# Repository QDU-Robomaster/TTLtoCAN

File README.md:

# 项目名称
TTLtoCANforTOF

## 项目简介
面向 ToF 设备的 TTL UART 转 CAN 通信模块，设计目标是通过 24V 输入为 ToF 提供 5V 电源，并由 STM32 完成串口数据与 CAN 报文之间的转换。

## PCB预览

以下预览基于 2026-10-05 21:07 保存的 PCB 文件重新生成。部分器件未配置三维模型，实际装配以封装和 BOM 为准。

正面：

背面：

## 主要参数
PCB 尺寸  36.00 × 20.05 mm，圆角矩形 
层数 / 板厚  2 层 / 1.6 mm 
输入电源  设计标称 24V，经 J4 输入 
ToF 电源  设计目标 5V，经 J3 第 4 脚输出 
板上逻辑电源  3.3V 
主控  STM32G0B1CBTx，LQFP-48 
通信接口  UART（J3）、CAN（J2） 
调试接口  SWD（J6） 
## 接口定义
J4：电源输入 AMASS XT30U-F，2Pin  
    1：GND；
    2：VCC_IN（标称 24V 输入） 
J2：CAN  JST GH，2Pin，1.25 mm  
    1：CAN− / CAN_L；
    2：CAN+ / CAN_H 
J3：ToF  JST GH，4Pin，1.25 mm  
    1：USART1_TX（模块输出，接设备 RX）；
    2：USART1_RX（模块输入，接设备 TX）；
    3：GND；
    4：5V 电源输出 
J6：SWD  Molex CLIK-Mate 502386-0470，4Pin，1.25 mm  
    1：SWDIO；
    2：SWCLK；
    3：GND；
    4：3.3V 参考电源 
## 项目扩展叙述

电源部分通过 TPS54202 将输入电源降压至设计目标 5V，再由 ME6211 产生板上 3.3V。STM32 连接 ToF 的 UART，并通过 CAN 收发器接入总线。通信转换需要配套固件，当前仓库未提供固件及协议定义。

详细的接口接线、工程打开方式、生产资料与调试安排见 [工程说明文档](Documents/工程说明.md)。

## 主要器件
U1  TPS54202DDC  开关降压，设计用于产生 5V 
U2  ME6211C33M5  3.3V 线性稳压 
U3  STM32G0B1CBTx  通信处理主控 
U6  TCAN3413DR（当前 Value）  CAN 收发器
Q2  Si2309CDS-T1-GE3  输入侧 P 沟道 MOS 管 
D3  BZT52-C12  输入保护电路中的稳压管 
L1  15µH  降压电感 
Y1  X32258MSB  MCU 外部晶振
## 制造资料指路
制造和装配输出位于 [Production_documents/](Production_documents/)，各子目录用途见 [工程说明文档](Documents/工程说明.md)。
使用 KiCad 10.0.x 打开根目录的 [TTLtoCANforTOF.kicad_pro](TTLtoCANforTOF.kicad_pro)，再进入原理图或 PCB 编辑器。
 [TTLtoCANforTOF.kicad_sch](TTLtoCANforTOF.kicad_sch)  当前原理图 
 [TTLtoCANforTOF.kicad_pcb](TTLtoCANforTOF.kicad_pcb)  当前 PCB 
 [sym-lib-table](sym-lib-table)  项目符号库路径配置  [BOM/](BOM/)  设计物料清单 
 [Documents/](Documents/)  项目说明、预览图和检查报告 
 [3Dmodel/TTLtoCANforTOF.step](3Dmodel/TTLtoCANforTOF.step)  整板 STEP 模型 
 [Production_documents/](Production_documents/)  生产输出资料 
 [History/](History/)  历史工程快照，不作为当前生产依据

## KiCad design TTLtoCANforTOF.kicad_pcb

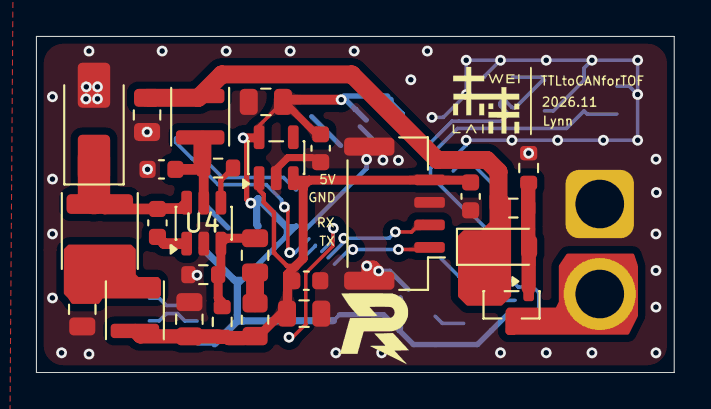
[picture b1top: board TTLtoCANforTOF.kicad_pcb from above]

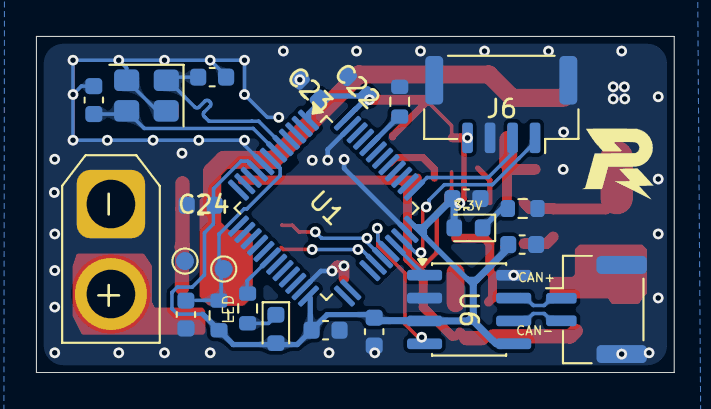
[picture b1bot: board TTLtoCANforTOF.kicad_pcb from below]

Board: 2 copper layers, 35.4 x 18.7 mm, 50 parts (24 on the bottom side), 28 nets.

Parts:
C1, C2, C10, C12, C13, C18, C19, C20, C21, C22, C23, C24: 0.1uF; C_0603_1608Metric
C3: 4.7uF; C_0805_2012Metric
C4: C_Small; C_0805_2012Metric
C5, C6, C9: 10uF; C_0805_2012Metric
C11: 22uF; C_0805_2012Metric
C15: 4.7uF; C_0603_1608Metric
C16, C17: 22pF; C_0603_1608Metric
D1, D2: LED; LED_0603_1608Metric
D3: BZT52-C12; D_SOD-123
D4: SS16; D_SMA
J2: CAN; JST_GH_BM02B-GHS-TBT_1x02-1MP_P1.25mm_Vertical
J3: TOF; JST_GH_BM04B-GHS-TBT_1x04-1MP_P1.25mm_Vertical
J4: XT30; AMASS_XT30U-F_1x02_P5.0mm_Vertical
J6: SWD; Molex_CLIK-Mate_502386-0470_1x04-1MP_P1.25mm_Horizontal
L1, L3: 10uH; L_Changjiang_FNR3010S
L2: 15uH; L_Changjiang_FNR4020S
Q2: Si2309CDS-T1-GE3; SOT-23
R1: 1MΩ; R_0603_1608Metric
R2: R_Small; R_0805_2012Metric
R4: 62kΩ; R_0603_1608Metric
R5: 12kΩ; R_0603_1608Metric
R6, R8: 10kΩ; R_0603_1608Metric
R7, R9: 100kΩ; R_0603_1608Metric
R10, R11: 1kΩ; R_0603_1608Metric
TP1: RST; TestPoint_Pad_D1.0mm
TP2: GND; TestPoint_Pad_D1.0mm
U1: STM32F103C8Tx; LQFP-48_7x7mm_P0.5mm
U2: ME6211C33M5; SOT-23-5
U4: TD1466tr; SOT-23-6
U6: TCAN3413DR; SOIC-8_3.9x4.9mm_P1.27mm
Y1: X32258MSB; Crystal_SMD_3225-4Pin_3.2x2.5mm

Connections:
5V: C6.2, C9.1, C10.1, C20.2, J3.4, L3.2, R2.2, R4.1, U2.1 (V_{IN}), U2.3 (CE)
+3.3V: C11.1, C12.1, C13.1, C15.1, C19.1, C21.1, C22.1, C23.1, C24.1, D1.2 (A), D2.2 (A), J6.4, R6.1, U1.1 (VBAT), U1.9 (VDDA), U1.24 (VDD), U1.36 (VDD), U1.48 (VDD), U2.5 (V_{OUT}), U6.3 (VCC), U6.5 (VIO)
+24V: C3.2, D3.1 (K), L1.1, Q2.2 (S), R9.1
/CAN+: J2.1, U6.7 (CANH)
/CAN-: J2.2, U6.6 (CANL)
/CAN_RX: U1.32 (PA11), U6.4 (RXD)
/CAN_TX: U1.33 (PA12), U6.1 (TXD)
/LED: R11.2, U1.18 (PB0)
/NRST: C18.1, R6.2, TP1.1 (1_1), U1.7 (NRST)
/OSC+: C16.2, U1.5 (PD0), Y1.1
/OSC-: C17.2, U1.6 (PD1), Y1.3
/SWCLK: J6.2, U1.37 (PA14)
/SWDIO: J6.1, U1.34 (PA13)
/USART1_RX: J3.2, U1.31 (PA10)
/USART1_TX: J3.1, U1.30 (PA9)
GND: C2.1, C3.1, C5.1, C6.1, C9.2, C10.2, C11.2, C12.2, C13.2, C15.2, C16.1, C17.1, C18.2, C19.2, C20.1, C21.2, C22.2, C23.2, C24.2, D4.2 (A), J2.MP (MountPin), J3.3, J3.MP (MountPin), J4.1, J6.3, J6.MP (MountPin), R5.2, R7.1, R8.1, R10.2, TP2.1 (1_1), U1.8 (VSSA), U1.23 (VSS), U1.35 (VSS), U1.47 (VSS), U2.2 (V_{SS}), U4.2 (GND), U6.2 (GND), U6.8 (STB), Y1.2, Y1.4
unnamed: C4.2, R2.1
unnamed: C5.2, L2.1, L3.1
unnamed: D1.1 (K), R10.1
unnamed: D2.1 (K), R11.1
unnamed: D3.2 (A), Q2.1 (G), R8.2, R9.2
unnamed: C1.2, D4.1 (K), L2.2, U4.6 (SW)
unnamed: R7.2, U1.44 (BOOT0)
unnamed: C1.1, U4.1 (BS)
unnamed: R1.2, U4.4 (EN)
unnamed: C4.1, R4.2, R5.1, U4.3 (FB)
unnamed: C2.2, L1.2, R1.1, U4.5 (VIN)
VCC_IN: J4.2, Q2.3 (D)

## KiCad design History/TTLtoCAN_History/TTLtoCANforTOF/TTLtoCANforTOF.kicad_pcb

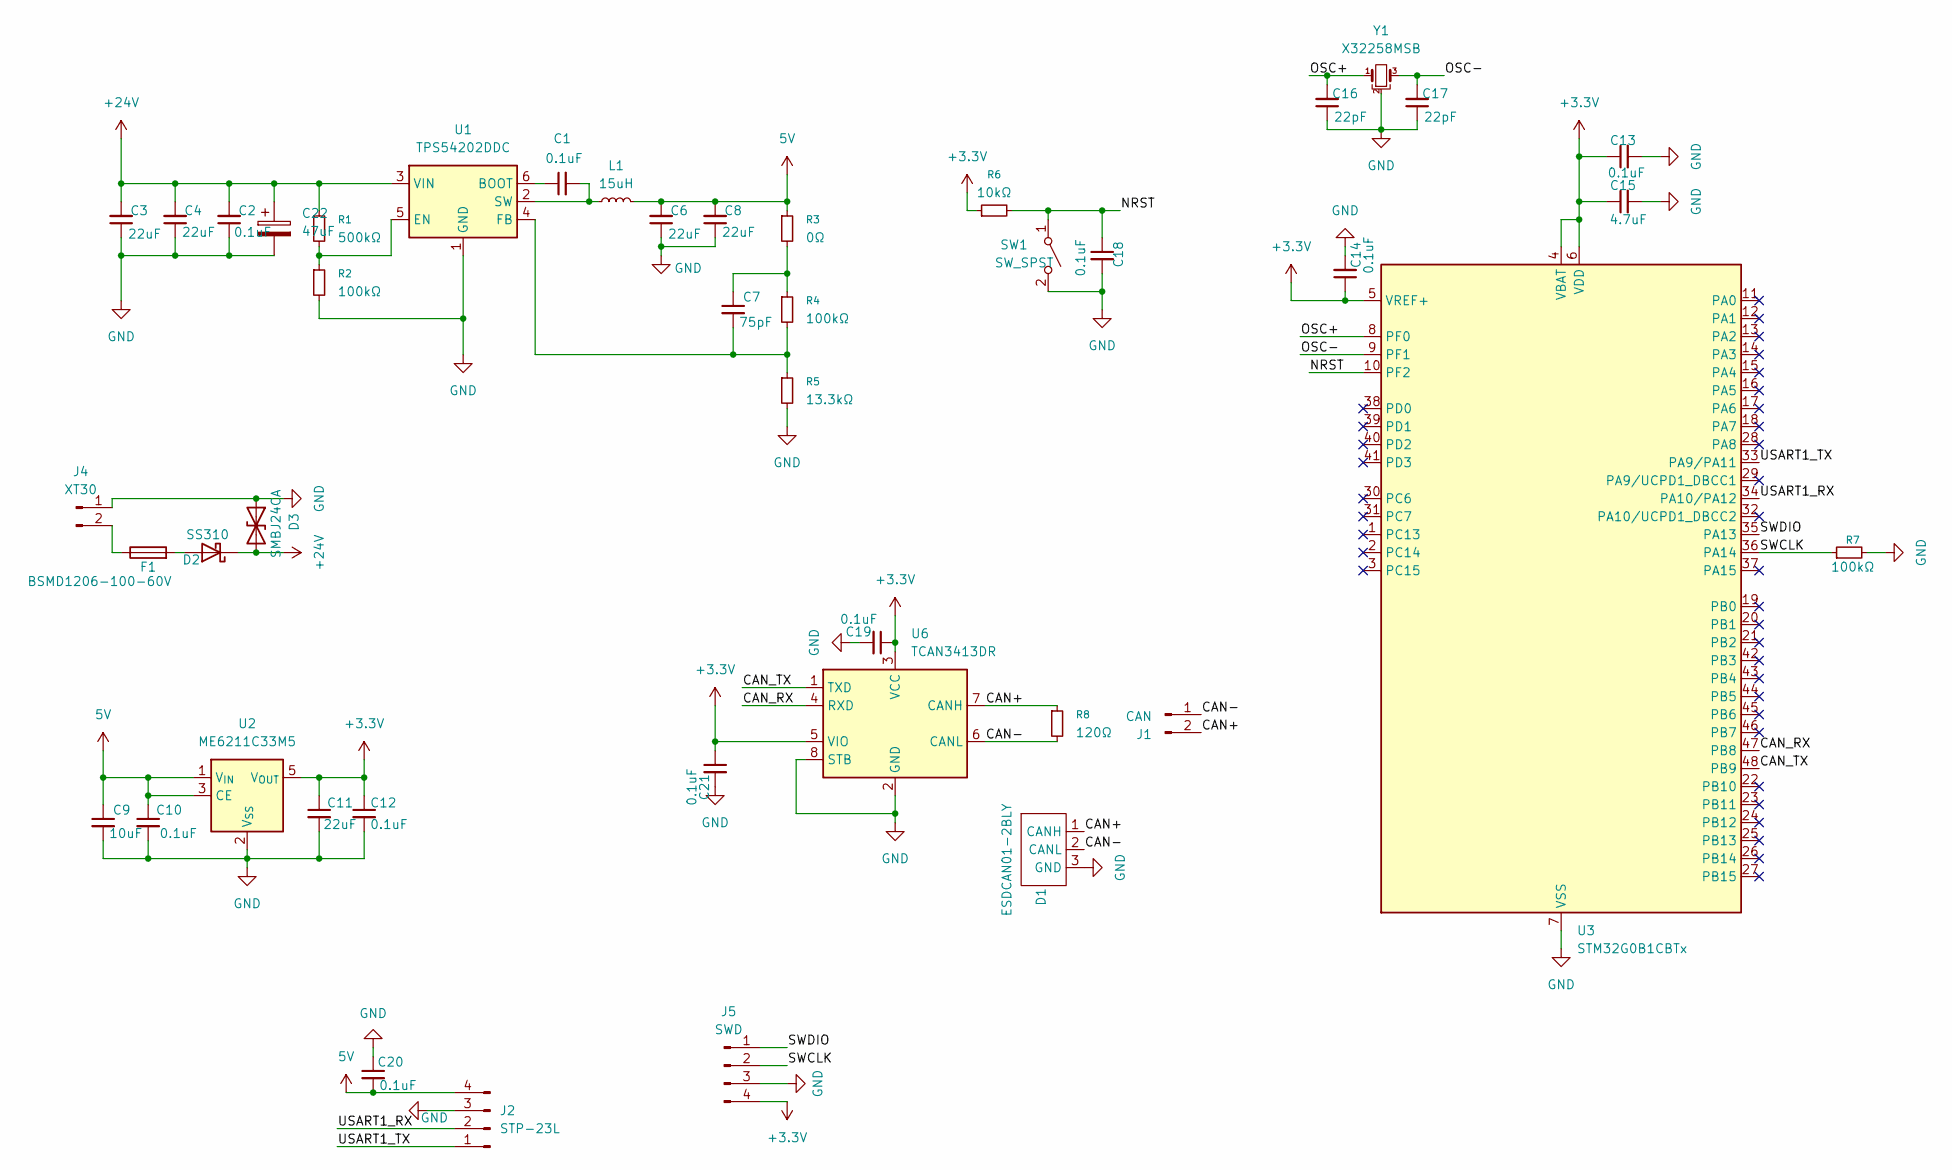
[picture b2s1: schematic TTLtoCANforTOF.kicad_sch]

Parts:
C1, C2, C10, C12, C13, C14, C18, C19, C20, C21: 0.1uF; C_0603_1608Metric
C3, C4: 22uF; C_1210_3225Metric
C6, C8, C11: 22uF; C_0805_2012Metric
C7: 75pF; C_0603_1608Metric
C9: 10uF; C_0805_2012Metric
C15: 4.7uF; C_0603_1608Metric
C16, C17: 22pF; C_0603_1608Metric
C22: 47uF; C_Elec_6.3x7.7
D1: ESDCAN01-2BLY; SOT-23-3
D2: SS310; D_SMA
D3: SMBJ24CA; D_SMB
F1: BSMD1206-100-60V; Fuse_1206_3216Metric
J1: CAN; JST_GH_SM02B-GHS-TB_1x02-1MP_P1.25mm_Horizontal
J2: STP-23L; JST_GH_SM04B-GHS-TB_1x04-1MP_P1.25mm_Horizontal
J4: XT30; AMASS_XT30U-F_1x02_P5.0mm_Vertical
J5: SWD; Molex_CLIK-Mate_502386-0470_1x04-1MP_P1.25mm_Horizontal
L1: 15uH; L_7.3x7.3_H3.5
R1: 500kΩ; R_0603_1608Metric
R2, R4, R7: 100kΩ; R_0603_1608Metric
R3: 0Ω; R_0805_2012Metric
R5: 13.3kΩ; R_0603_1608Metric
R6: 10kΩ; R_0603_1608Metric
R8: 120Ω; R_1206_3216Metric
SW1: SW_SPST; SW_SPST_B3U-1000P
U1: TPS54202DDC; SOT-23-6
U2: ME6211C33M5; SOT-23-5
U3: STM32G0B1CBTx; LQFP-48_7x7mm_P0.5mm
U6: TCAN3413DR; SOIC-8_3.9x4.9mm_P1.27mm
Y1: X32258MSB; Crystal_SMD_3225-4Pin_3.2x2.5mm

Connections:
5V: C6.2, C8.2, C9.1, C10.1, C20.2, J2.4, L1.1, R3.1, U2.1 (V_{IN}), U2.3 (CE)
+3.3V: C11.1, C12.1, C13.1, C14.1, C15.1, C19.1, C21.1, J5.4, R6.1, U2.5 (V_{OUT}), U3.4 (VBAT), U3.5 (VREF+), U3.6 (VDD), U6.3 (VCC), U6.5 (VIO)
+24V: C2.2, C3.2, C4.2, C22.1, D2.1 (K), D3.2 (A2), R1.1, U1.3 (VIN)
/CAN+: D1.1 (CANH), J1.2, R8.1, U6.7 (CANH)
/CAN-: D1.2 (CANL), J1.1, R8.2, U6.6 (CANL)
/CAN_RX: U3.47 (PB8), U6.4 (RXD)
/CAN_TX: U3.48 (PB9), U6.1 (TXD)
/NRST: C18.1, R6.2, SW1.1 (A), U3.10 (PF2)
/OSC+: C16.2, U3.8 (PF0), Y1.1
/OSC-: C17.2, U3.9 (PF1), Y1.3
/SWCLK: J5.2, R7.1, U3.36 (PA14)
/SWDIO: J5.1, U3.35 (PA13)
/USART1_RX: J2.2, U3.34 (PA10/PA12)
/USART1_TX: J2.1, U3.33 (PA9/PA11)
GND: C2.1, C3.1, C4.1, C6.1, C8.1, C9.2, C10.2, C11.2, C12.2, C13.2, C14.2, C15.2, C16.1, C17.1, C18.2, C19.2, C20.1, C21.2, C22.2, D1.3 (GND), D3.1 (A1), J1.MP, J2.3, J2.MP, J4.1, J5.3, J5.MP, R2.2, R5.2, R7.2, SW1.2 (B), U1.1 (GND), U2.2 (V_{SS}), U3.7 (VSS), U6.2 (GND), U6.8 (STB), Y1.2, Y1.4
unnamed: C7.1, R3.2, R4.1
unnamed: D2.2 (A), F1.2
unnamed: F1.1, J4.2
unnamed: C1.1, U1.6 (BOOT)
unnamed: R1.2, R2.1, U1.5 (EN)
unnamed: C7.2, R4.2, R5.1, U1.4 (FB)
unnamed: C1.2, L1.2, U1.2 (SW)

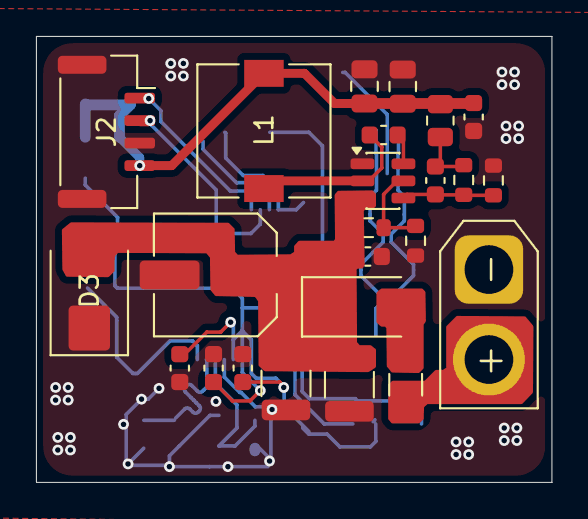
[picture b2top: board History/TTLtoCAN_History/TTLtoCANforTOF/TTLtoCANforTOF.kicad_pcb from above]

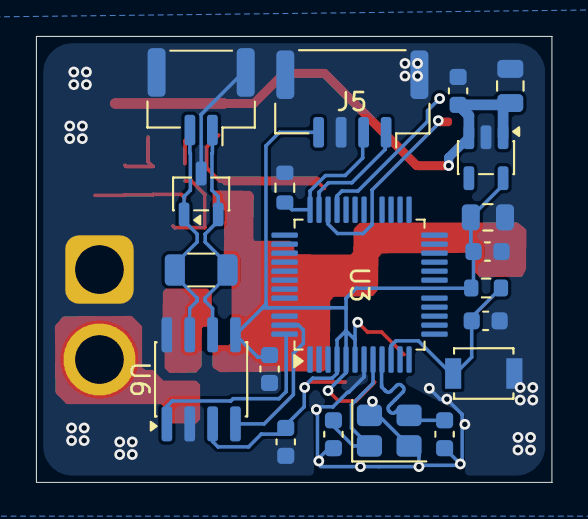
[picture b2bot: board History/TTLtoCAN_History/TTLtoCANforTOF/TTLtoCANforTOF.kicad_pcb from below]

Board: 2 copper layers, 28.6 x 24.8 mm, 44 parts (20 on the bottom side), 22 nets.
